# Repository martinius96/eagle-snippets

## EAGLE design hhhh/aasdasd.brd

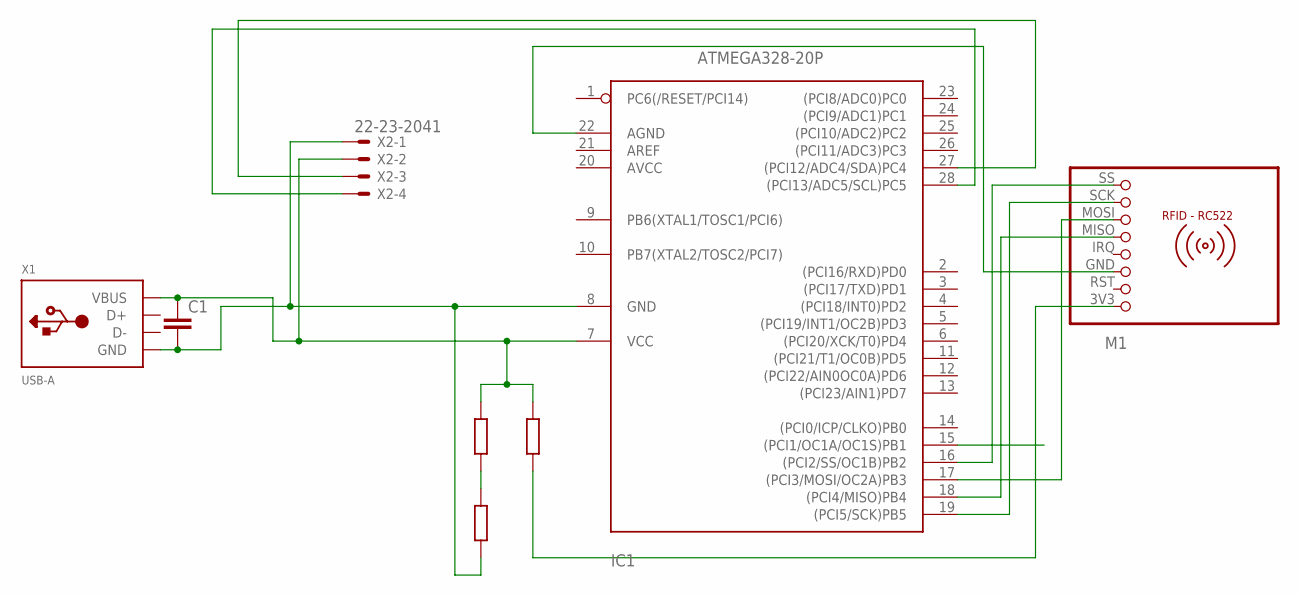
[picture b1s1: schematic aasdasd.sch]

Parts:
C1: C-EU025-050X050; C025-050X050
IC1: ATMEGA328-20P; DIL28-3
M1: RFID-RC522
X1: USB-A; MOLEX_480371000
X2: 22-23-2041

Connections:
unnamed: C1.2, IC1.8 (GND), X1.4 (GND), X2.1
unnamed: IC1.19 ((PCI5/SCK)PB5), M1.SCK (7)
unnamed: IC1.18 ((PCI4/MISO)PB4), M1.MISO (5)
unnamed: IC1.22 (AGND), M1.GND (3)
unnamed: IC1.16 ((PCI2/SS/OC1B)PB2), M1.SS (8)
unnamed: IC1.17 ((PCI3/MOSI/OC2A)PB3), M1.MOSI (6)
unnamed: IC1.27 ((PCI12/ADC4/SDA)PC4), X2.3
unnamed: IC1.28 ((PCI13/ADC5/SCL)PC5), X2.4
unnamed: C1.1, IC1.7 (VCC), X1.1 (VBUS), X2.2

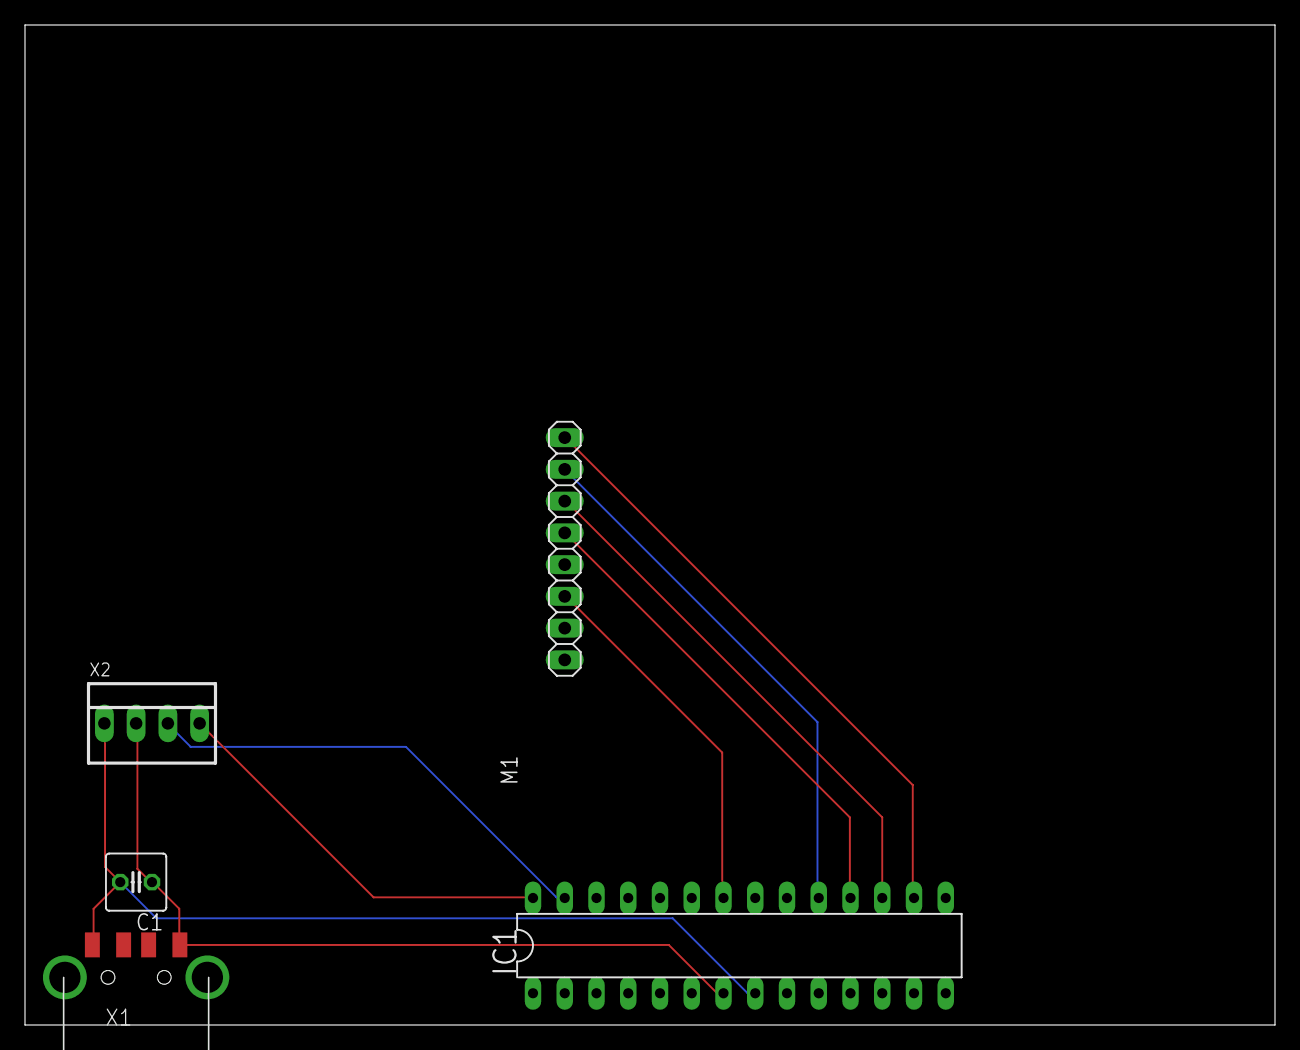
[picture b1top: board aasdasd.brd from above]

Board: 2 copper layers, 100.0 x 80.0 mm, 5 parts (0 on the bottom side), 9 nets.

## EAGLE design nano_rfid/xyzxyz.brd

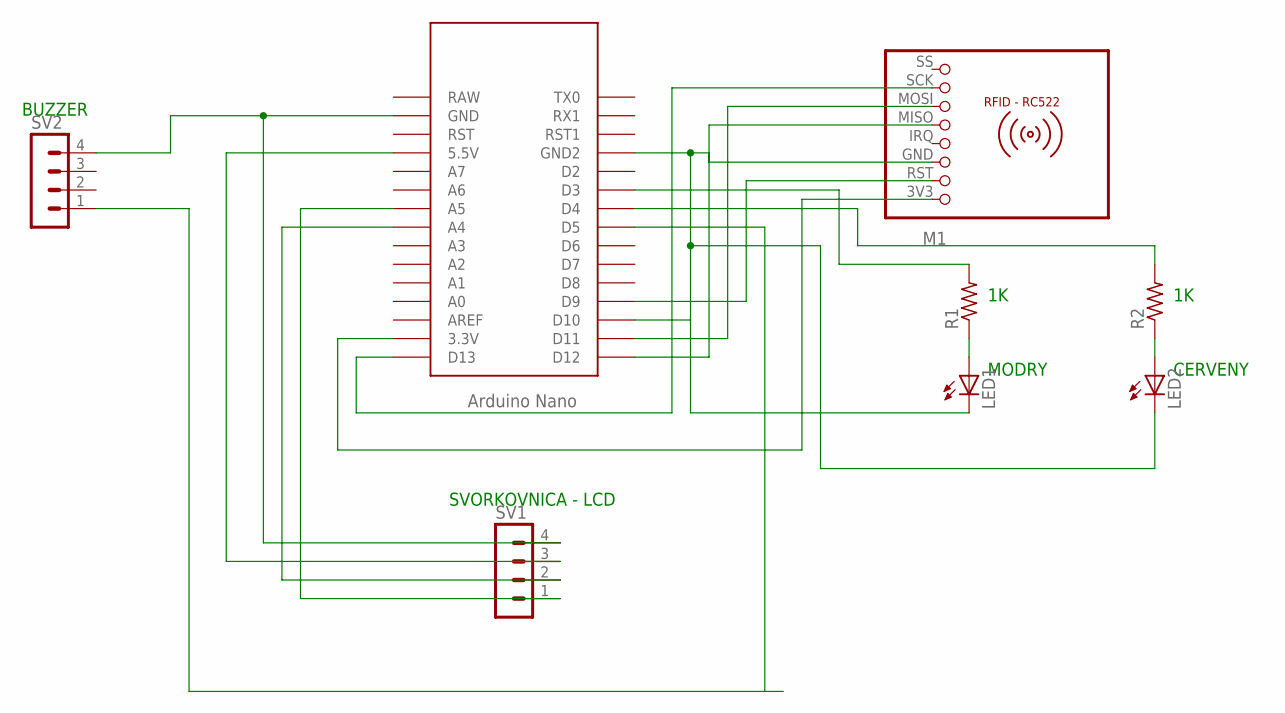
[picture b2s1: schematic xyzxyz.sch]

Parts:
LED1, LED2: LED3MM
M1: RFID-RC522
R1, R2: R-US_0414/15; 0414/15
SV1, SV2: MA04-1
U$1: NANO

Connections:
unnamed: M1.3V3 (1), U$1.3.3V
unnamed: LED1.K (C), LED2.K (C), M1.GND (3), U$1.GND1 (GND2)
unnamed: M1.RST (2), U$1.D9
unnamed: M1.MISO (5), U$1.D12
unnamed: M1.MOSI (6), U$1.D11
unnamed: M1.SCK (7), U$1.D13
unnamed: SV1.4, SV2.4, U$1.GND
unnamed: SV1.3, U$1.5V (5.5V)
unnamed: SV1.2, U$1.A4
unnamed: SV1.1, U$1.A5
unnamed: LED1.A, R1.1
unnamed: LED2.A, R2.1
unnamed: R1.2, U$1.D3
unnamed: R2.2, U$1.D4
unnamed: SV2.1, U$1.D5

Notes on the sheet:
SVORKOVNICA - LCD
BUZZER
MODRY
CERVENY

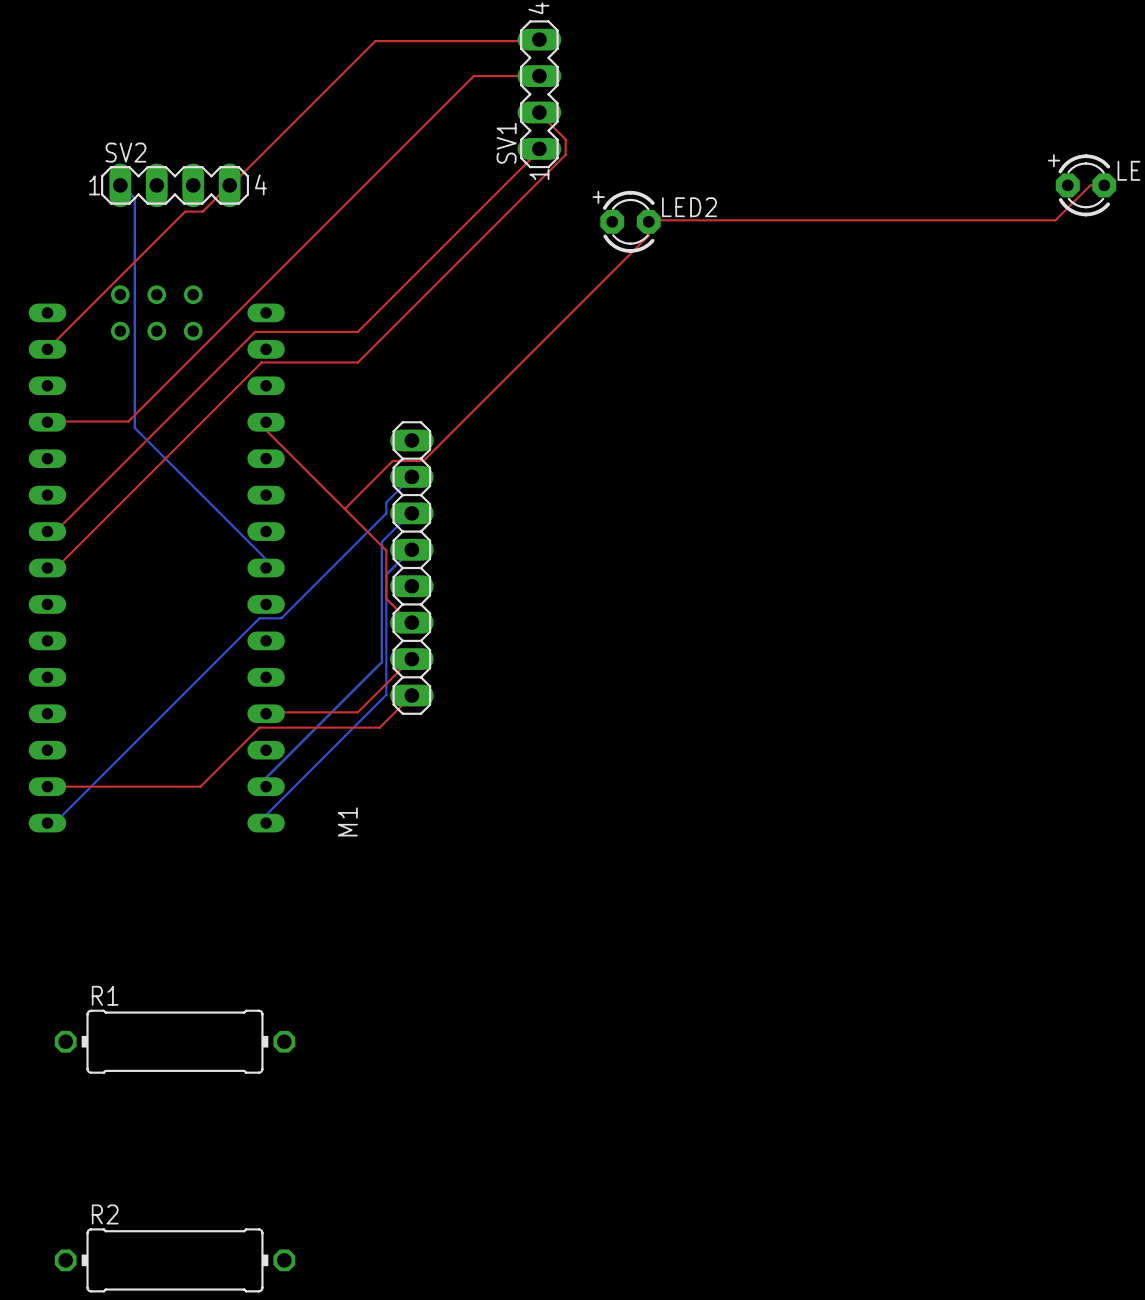
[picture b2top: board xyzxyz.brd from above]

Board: 2 copper layers, 8 parts (1 on the bottom side), 15 nets.

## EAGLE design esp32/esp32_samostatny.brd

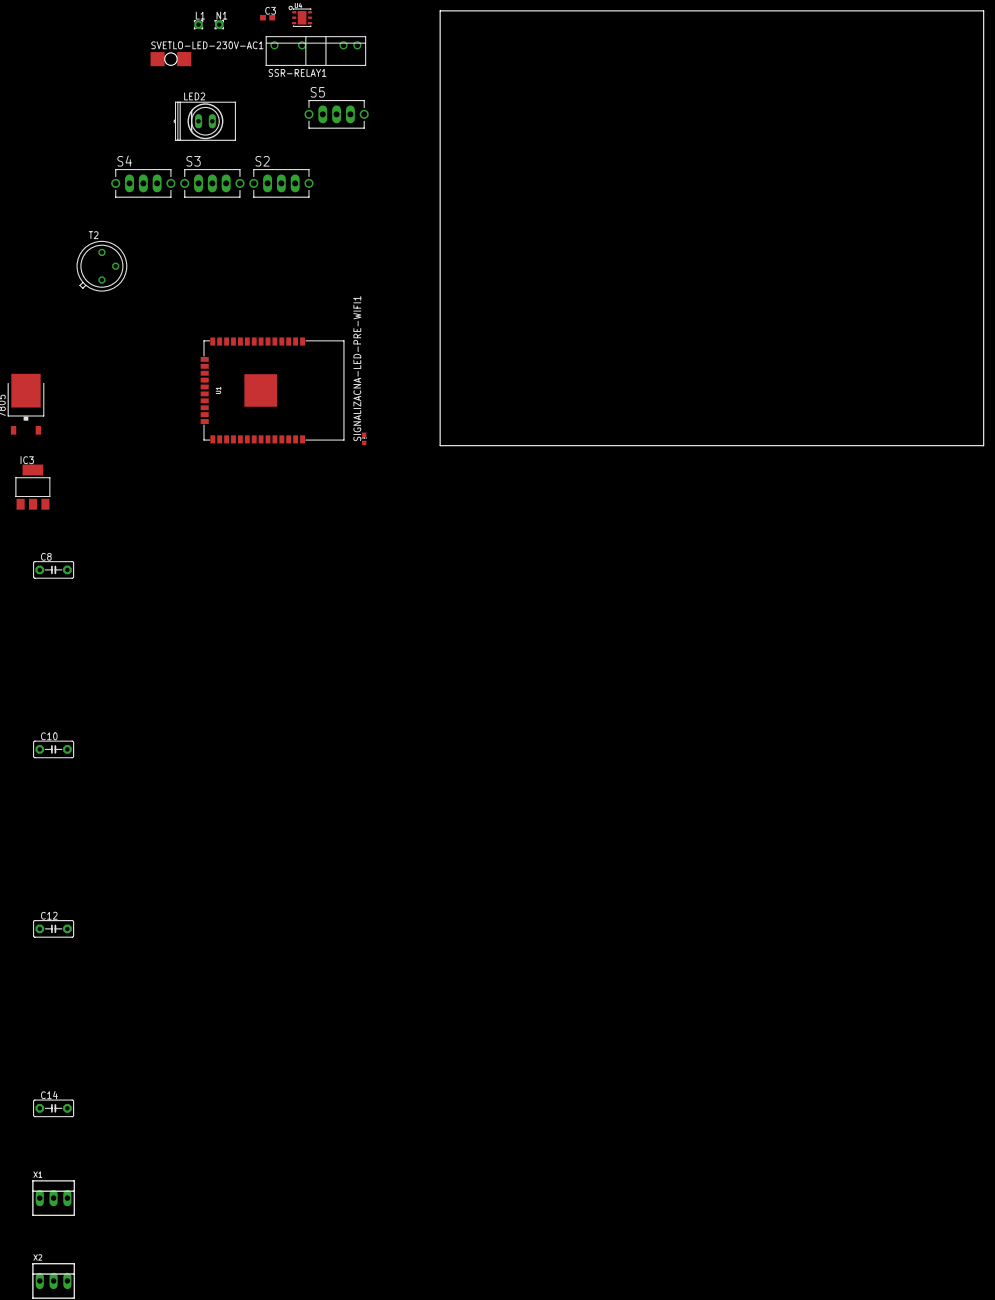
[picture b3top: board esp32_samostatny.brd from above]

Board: 2 copper layers, 100.0 x 80.0 mm, 22 parts (0 on the bottom side), 15 nets, no tracks yet.

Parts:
7805: LP2950; DPACK
C3: 10uF; C0603
C8, C12: 100uF; C5B3
C10, C14: 10uF; C5B3
IC3: 1117-3.3; SOT223
L1: 1,6/0,8
LED2: Q62902-B153
N1: 1,6/0,8
S2, S3, S4, S5: TL32YO; TL3XYO
SIGNALIZACNA-LED-PRE-WIFI1: CHIP-LED0603
SSR-RELAY1: S202S02
SVETLO-LED-230V-AC1: LYP4-BOTTOM; P47F-BOTTOM
T2: 2N1613; TO5
U1: ESP-WROOM-32
U4: Si7021-A20; DFN6_3X3_SI
X1, X2: 22-23-2031

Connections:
EN: S2.2, S3.2, U1.3, X1.1
GND: 7805.2, C3.2, C8.2, C10.2, C12.2, C14.2, IC3.1, S2.3, S3.3, T2.1, U1.1, U1.15, U1.24, U1.GND
IO21: U1.33, U4.1
IO22: U1.36, U4.6
unnamed: S4.3, S5.3
unnamed: S2.1, S3.1
unnamed: S4.1, S5.1
unnamed: SIGNALIZACNA-LED-PRE-WIFI1.C, U1.38, U4.2
unnamed: N1.1, SVETLO-LED-230V-AC1.C
unnamed: L1.1, SSR-RELAY1.2
unnamed: SSR-RELAY1.1, SVETLO-LED-230V-AC1.A
unnamed: 7805.3, C10.1, SSR-RELAY1.3
unnamed: SSR-RELAY1.4, T2.3
unnamed: LED2.K, U1.37
VCC: 7805.1, C3.1, C8.1, C12.1, C14.1, IC3.2, IC3.3, S4.2, S5.2, U1.2, U1.25, U4.5, X2.1

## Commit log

2019-12-20 Added Digitálny_podpis.png

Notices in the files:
parts and their libraries:
microbuilder: This work is placed in the public domain, and may be freely used for commercial and non-commercial work with the following conditions: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
